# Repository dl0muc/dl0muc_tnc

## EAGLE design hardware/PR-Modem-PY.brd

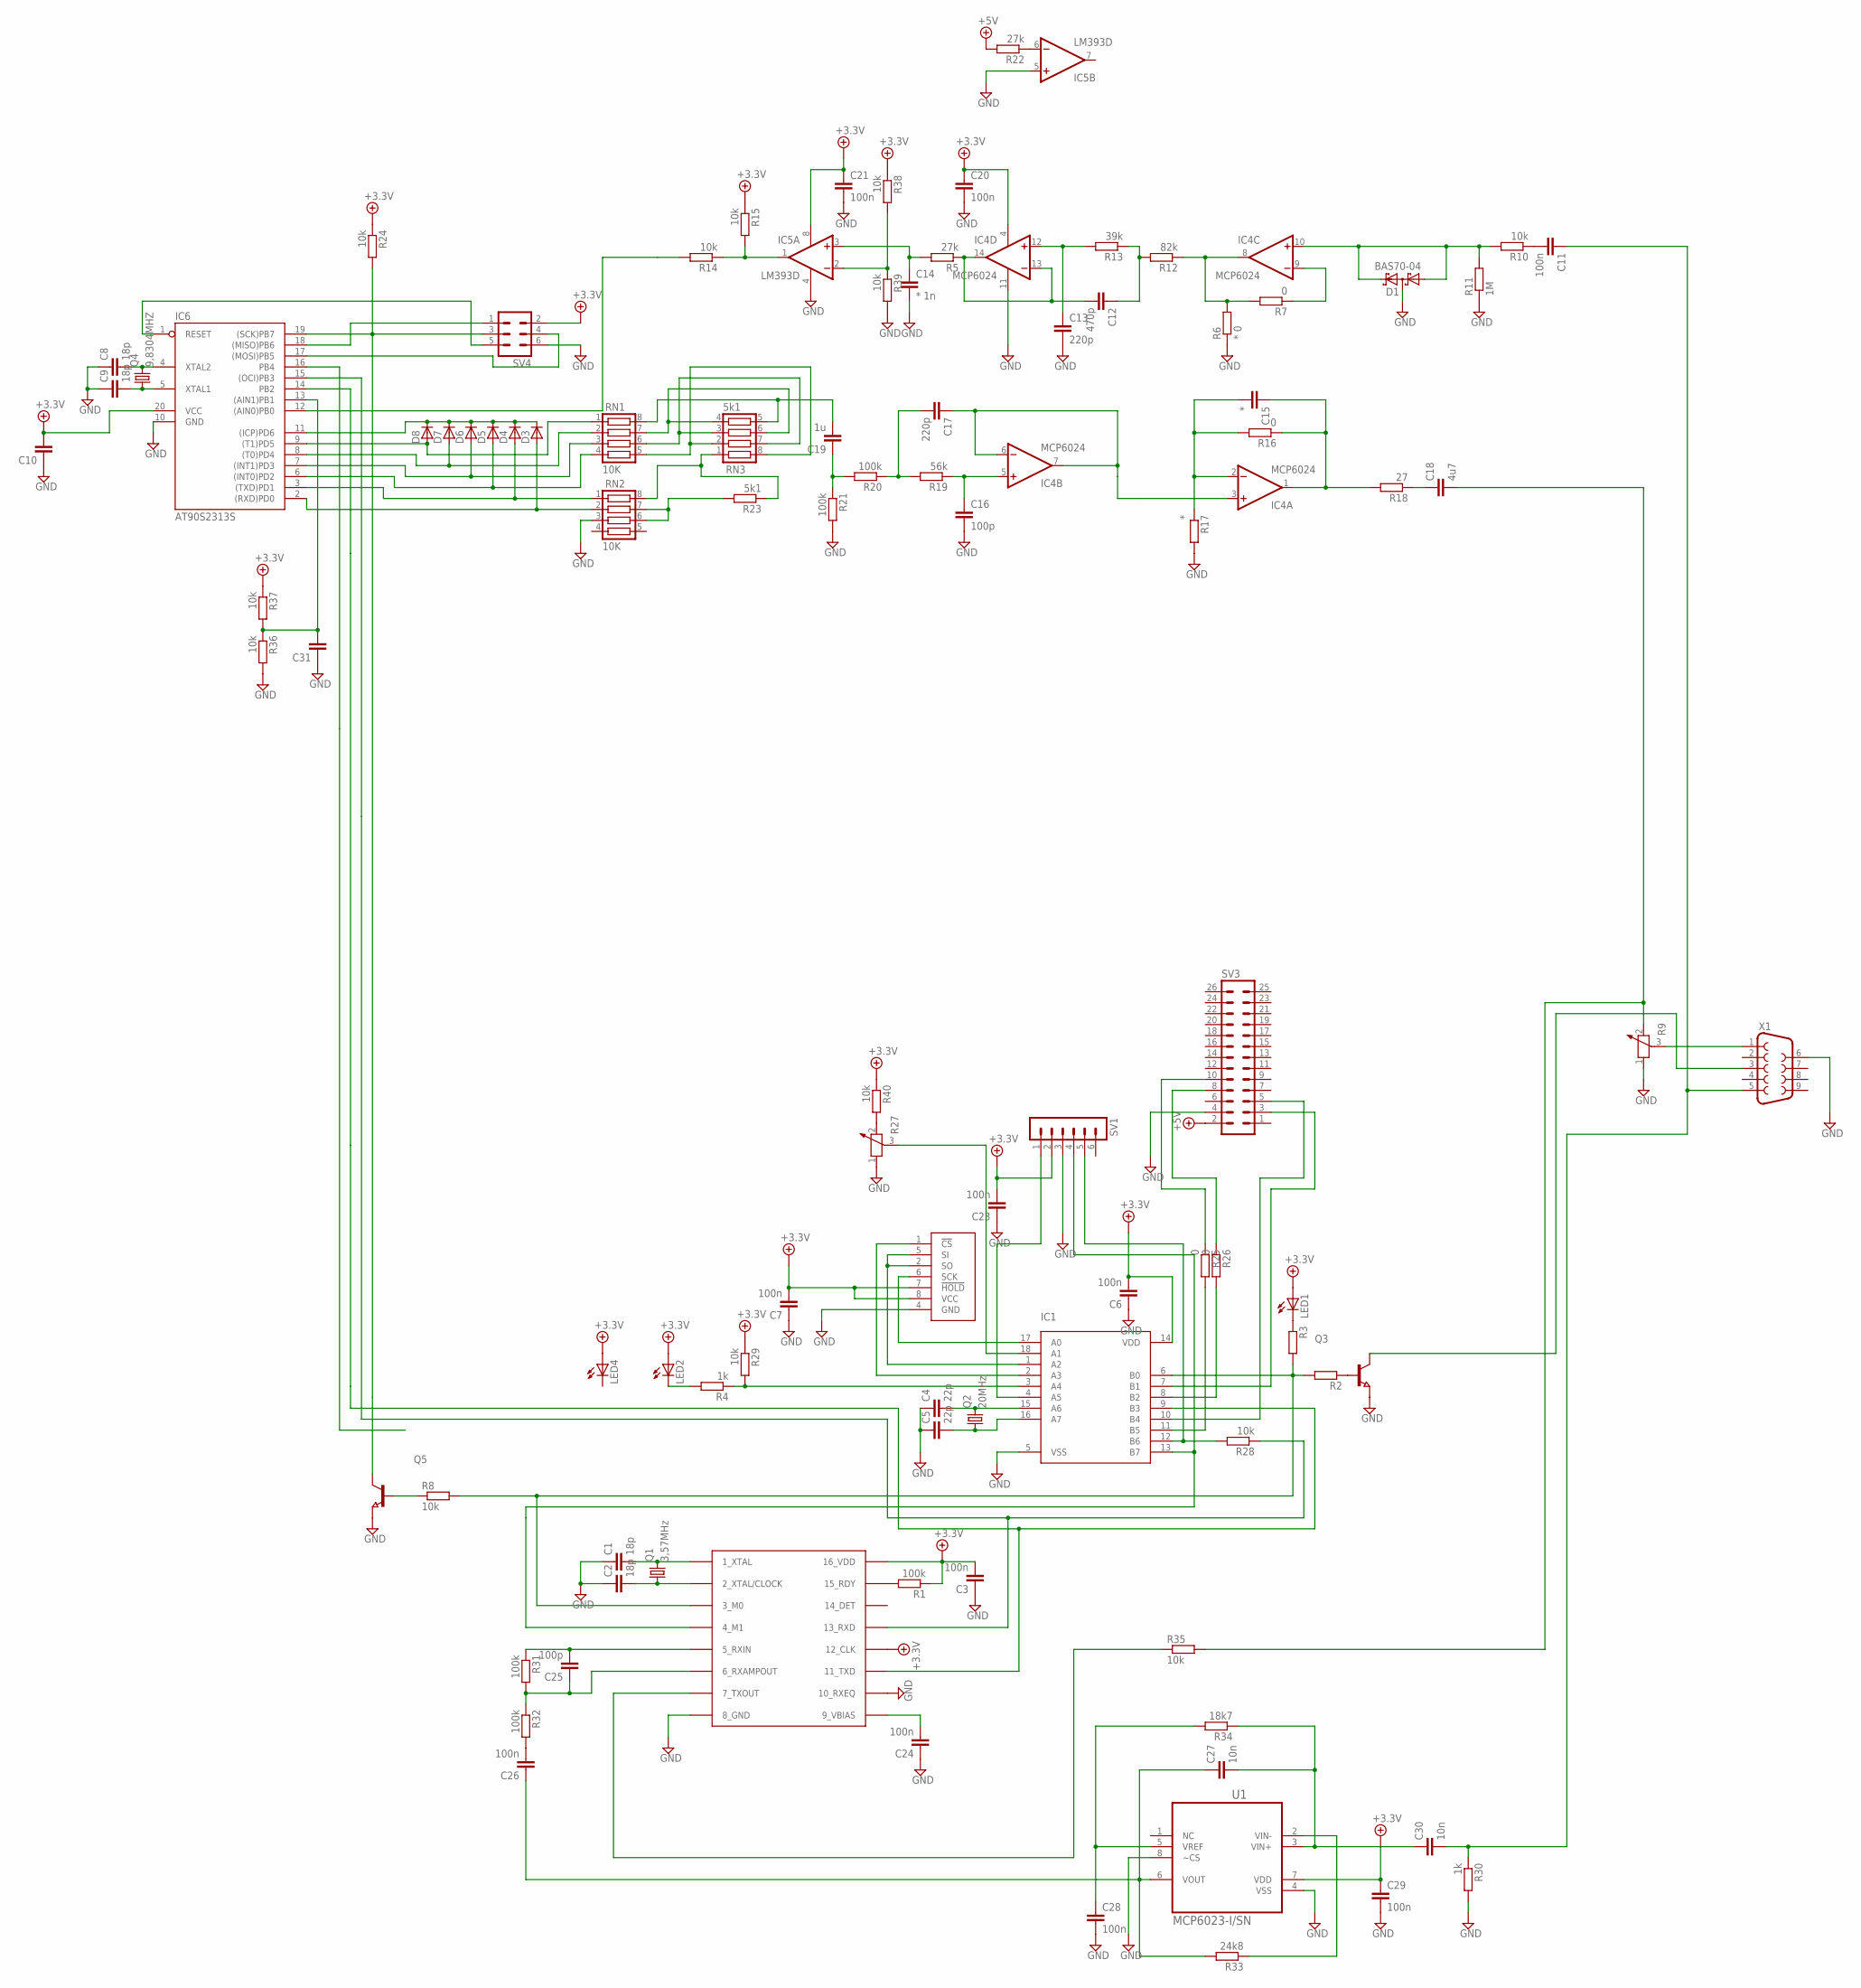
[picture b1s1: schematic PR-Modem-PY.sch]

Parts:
C1, C2, C8, C9: 18p; C0603
C3, C6, C7, C11, C20, C21, C23, C24, C26, C28, C29: 100n; C0603
C4, C5: 22p; C0603
C10, C31: C-EUC0603; C0603
C12: 470p; C0603
C13, C17: 220p; C0603
C14: * 1n; C0603
C15: *; C0603
C16, C25: 100p; C0603
C18: 4u7; C1210
C19: 1u; C1210
C27, C30: 10n; C0603
D1: BAS70-04; SOT23
D3, D4, D5, D6, D7, D8: D-SOD123; SOD123
IC1: PIC16F18X7SO; SOIC18-W
IC4: MCP6024; SO14
IC5: LM393D; SO08
IC6: AT90S2313S; SO20L
LED1, LED2, LED4: LED3MM
Q1: 3,57MHz; HC49/S
Q2: 20MHz; HC49/S
Q3, Q5: NPN-TRANSISTOR_SOT23; SOT23
Q4: 9,8304MHZ; HC49/S
R1, R20, R21, R31, R32: 100k; R0603
R2, R3: R-EU_R0603; R0603
R4, R30: 1k; R0603
R5, R22: 27k; R0603
R6: * 0; R0603
R7, R16, R25, R26: 0; R0603
R8, R10, R14, R15, R24, R28, R29, R35, R36, R37, R38, R39, R40: 10k; R0603
R9, R27: POTENTIOMETER_PT-10; PT-10
R11: 1M; R0603
R12: 82k; R0603
R13: 39k; R0603
R17: *; R0603
R18: 27; R0603
R19: 56k; R0603
R23: 5k1; R0603
R33: 24k8; R0603
R34: 18k7; R0603
RN1, RN2: 10K; CTS742C083
RN3: 5k1; CTS742C083
SV1: MA06-1
SV3: MA13-2
SV4: MA03-2
U1: MCP6023-I/SN; SOIC127P600X175-8N
U$1: 23K640SN; SOIC8
U$2: MX614; SOIC16-3
X1: F09HP

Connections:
+3.3V: C3.2, C6.2, C7.2, C10.2, C20.1, C21.1, C23.2, C29.1, IC1.14 (VDD), IC4.4 (V+), IC5.8 (V+), IC6.20 (VCC), LED1.A, LED2.A, LED4.A, R1.1, R15.1, R24.1, R29.1, R37.1, R38.1, R40.1, SV1.2, SV4.2, U1.7 (VDD), U$1.7 (!HOLD), U$1.8 (VCC), U$2.12 (12_CLK), U$2.16 (16_VDD)
+5V: R22.2, SV3.2
GND: C1.1, C2.1, C3.1, C4.1, C5.1, C6.1, C7.1, C8.1, C9.1, C10.1, C13.2, C14.2, C16.2, C20.2, C21.2, C23.1, C24.1, C28.2, C29.2, C31.1, D1.3 (C1A2), IC1.5 (VSS), IC4.11 (V-), IC5.4 (V-), IC5.5 (+IN), IC6.10 (GND), Q3.2 (E), Q5.2 (E), R6.1, R9.1, R11.1, R17.2, R21.2, R27.1, R30.2, R36.2, R39.2, RN2.3, SV1.3, SV3.4, SV4.6, U1.4 (VSS), U1.8 (~CS), U$1.4 (GND), U$2.8 (8_GND), U$2.10 (10_RXEQ), X1.6
unnamed: C1.2, Q1.2, U$2.1 (1_XTAL)
unnamed: C2.2, Q1.1, U$2.2 (2_XTAL/CLOCK)
unnamed: R1.2, U$2.15 (15_RDY)
unnamed: IC6.15 ((OCI)PB3), R28.1, U$2.13 (13_RXD)
unnamed: C4.2, IC1.15 (A6), Q2.2
unnamed: C8.2, IC6.4 (XTAL2), Q4.2
unnamed: C5.2, IC1.16 (A7), Q2.1
unnamed: C25.2, R31.1, U$2.5 (5_RXIN)
unnamed: IC1.1 (A2), U$1.2 (SO), U$1.5 (SI)
unnamed: IC1.2 (A3), U$1.1 (!CS)
unnamed: IC1.17 (A0), U$1.6 (SCK)
unnamed: IC1.9 (B3), IC6.14 (PB2), U$2.11 (11_TXD)
unnamed: Q3.1 (B), R2.1
unnamed: C25.1, R31.2, R32.1, U$2.6 (6_RXAMPOUT)
unnamed: LED1.K (C), R3.1
unnamed: IC1.3 (A4), R4.1, R29.2
unnamed: LED2.K (C), R4.2
unnamed: IC1.6 (B0), R2.2, R3.2, R8.2, U$2.3 (3_M0)
unnamed: C9.2, IC6.5 (XTAL1), Q4.1
unnamed: IC1.13 (B7), SV1.4, U$2.4 (4_M1)
unnamed: IC1.12 (B6), R28.2, SV1.5
unnamed: C11.2, R10.1
unnamed: D1.1 (A1), D1.2 (C2), IC4.10 (+IN), R10.2, R11.2
unnamed: IC4.9 (-IN), R7.1
unnamed: IC4.8 (OUT), R6.2, R7.2, R12.1
unnamed: C14.1, IC5.3 (+IN), R5.2
unnamed: C12.1, R12.2, R13.1
unnamed: C13.1, IC4.12 (+IN), R13.2
unnamed: C12.2, IC4.13 (-IN), IC4.14 (OUT), R5.1
unnamed: IC5.1 (OUT), R14.1, R15.2
unnamed: C15.1, IC4.1 (OUT), R16.1, R18.2
unnamed: C15.2, IC4.2 (-IN), R16.2, R17.1
unnamed: C17.1, IC4.3 (+IN), IC4.6 (-IN), IC4.7 (OUT)
unnamed: R9.3, X1.1
unnamed: C16.1, IC4.5 (+IN), R19.1
unnamed: C17.2, R19.2, R20.1
unnamed: C19.1, R20.2, R21.1
unnamed: C18.1, R18.1
unnamed: IC5.6 (-IN), R22.1
unnamed: C19.2, RN1.8, RN3.5
unnamed: RN1.7, RN3.4, RN3.6
unnamed: RN1.6, RN3.3, RN3.7
unnamed: RN1.5, RN3.2, RN3.8
unnamed: R23.2, RN2.6, RN2.7
unnamed: R23.1, RN2.8, RN3.1
unnamed: D3.2 (A), IC6.2 ((RXD)PD0), RN2.2
unnamed: D4.2 (A), IC6.3 ((TXD)PD1), RN2.1
unnamed: D5.2 (A), IC6.6 ((INT0)PD2), RN1.4
unnamed: D6.2 (A), IC6.7 ((INT1)PD3), RN1.3
unnamed: D7.2 (A), IC6.8 ((T0)PD4), RN1.2
unnamed: D8.2 (A), IC6.9 ((T1)PD5), RN1.1
unnamed: D3.1 (C), D4.1 (C), D5.1 (C), D6.1 (C), D7.1 (C), D8.1 (C), IC6.11 ((ICP)PD6)
unnamed: IC6.12 ((AIN0)PB0), R14.2
unnamed: C24.2, U$2.9 (9_VBIAS)
unnamed: IC6.19 ((SCK)PB7), Q5.3 (C), R24.2, SV4.3
unnamed: C26.2, R32.2
unnamed: IC5.2 (-IN), R38.2, R39.1
unnamed: Q5.1 (B), R8.1
unnamed: C11.1, C30.2, R30.1, X1.5
unnamed: IC1.7 (B1), SV3.3
unnamed: IC1.10 (B4), SV3.5
unnamed: IC1.4 (A5), SV1.1
unnamed: C26.1, C27.1, R33.2, U1.6 (VOUT)
unnamed: R33.1, U1.2 (VIN-)
unnamed: C27.2, C30.1, R34.1, U1.3 (VIN+)
unnamed: C28.1, R34.2, U1.5 (VREF)
unnamed: C18.2, R9.2, R35.2
unnamed: IC1.11 (B5), R25.2
unnamed: R35.1, U$2.7 (7_TXOUT)
unnamed: R25.1, SV3.10
unnamed: IC6.18 ((MISO)PB6), SV4.1
unnamed: IC6.1 (RESET), SV4.5
unnamed: IC6.17 ((MOSI)PB5), SV4.4
unnamed: Q3.3 (C), X1.3
unnamed: IC1.8 (B2), R26.2
unnamed: C31.2, IC6.13 ((AIN1)PB1), R36.1, R37.2
unnamed: R26.1, SV3.8
unnamed: R27.2, R40.2
unnamed: IC1.18 (A1), R27.3

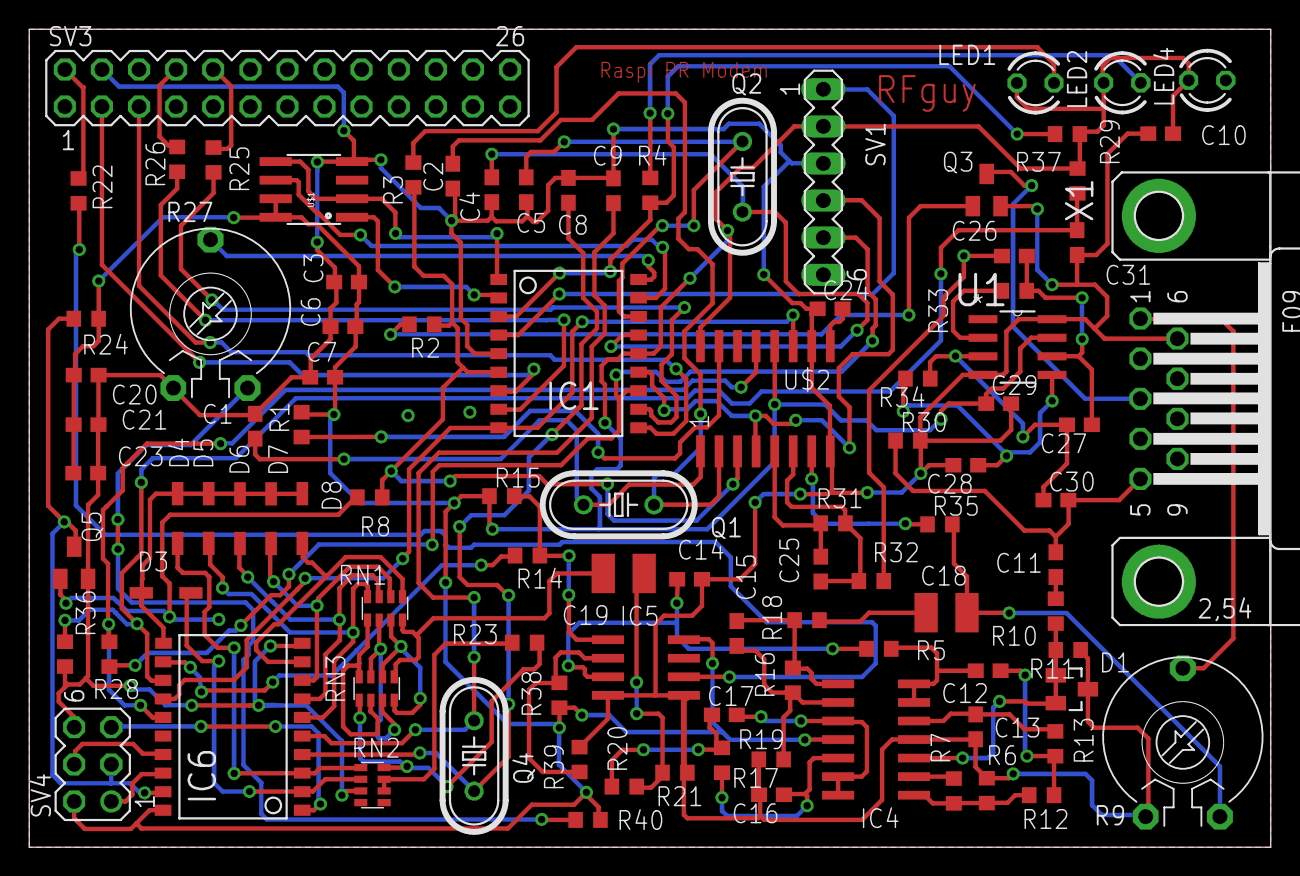
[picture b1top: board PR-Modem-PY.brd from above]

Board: 2 copper layers, 85.0 x 56.0 mm, 99 parts (0 on the bottom side), 82 nets.

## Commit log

2015-07-10 Packet Radio Modem für Raspberry PI 1k2 und 9k6 mit spice OP Amp berechnungen.
2015-07-10 changed directory structure

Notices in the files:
parts and their libraries:
SparkFun: Licensing: CC v3.0 Share-Alike You are welcome to use this library for commercial purposes.
